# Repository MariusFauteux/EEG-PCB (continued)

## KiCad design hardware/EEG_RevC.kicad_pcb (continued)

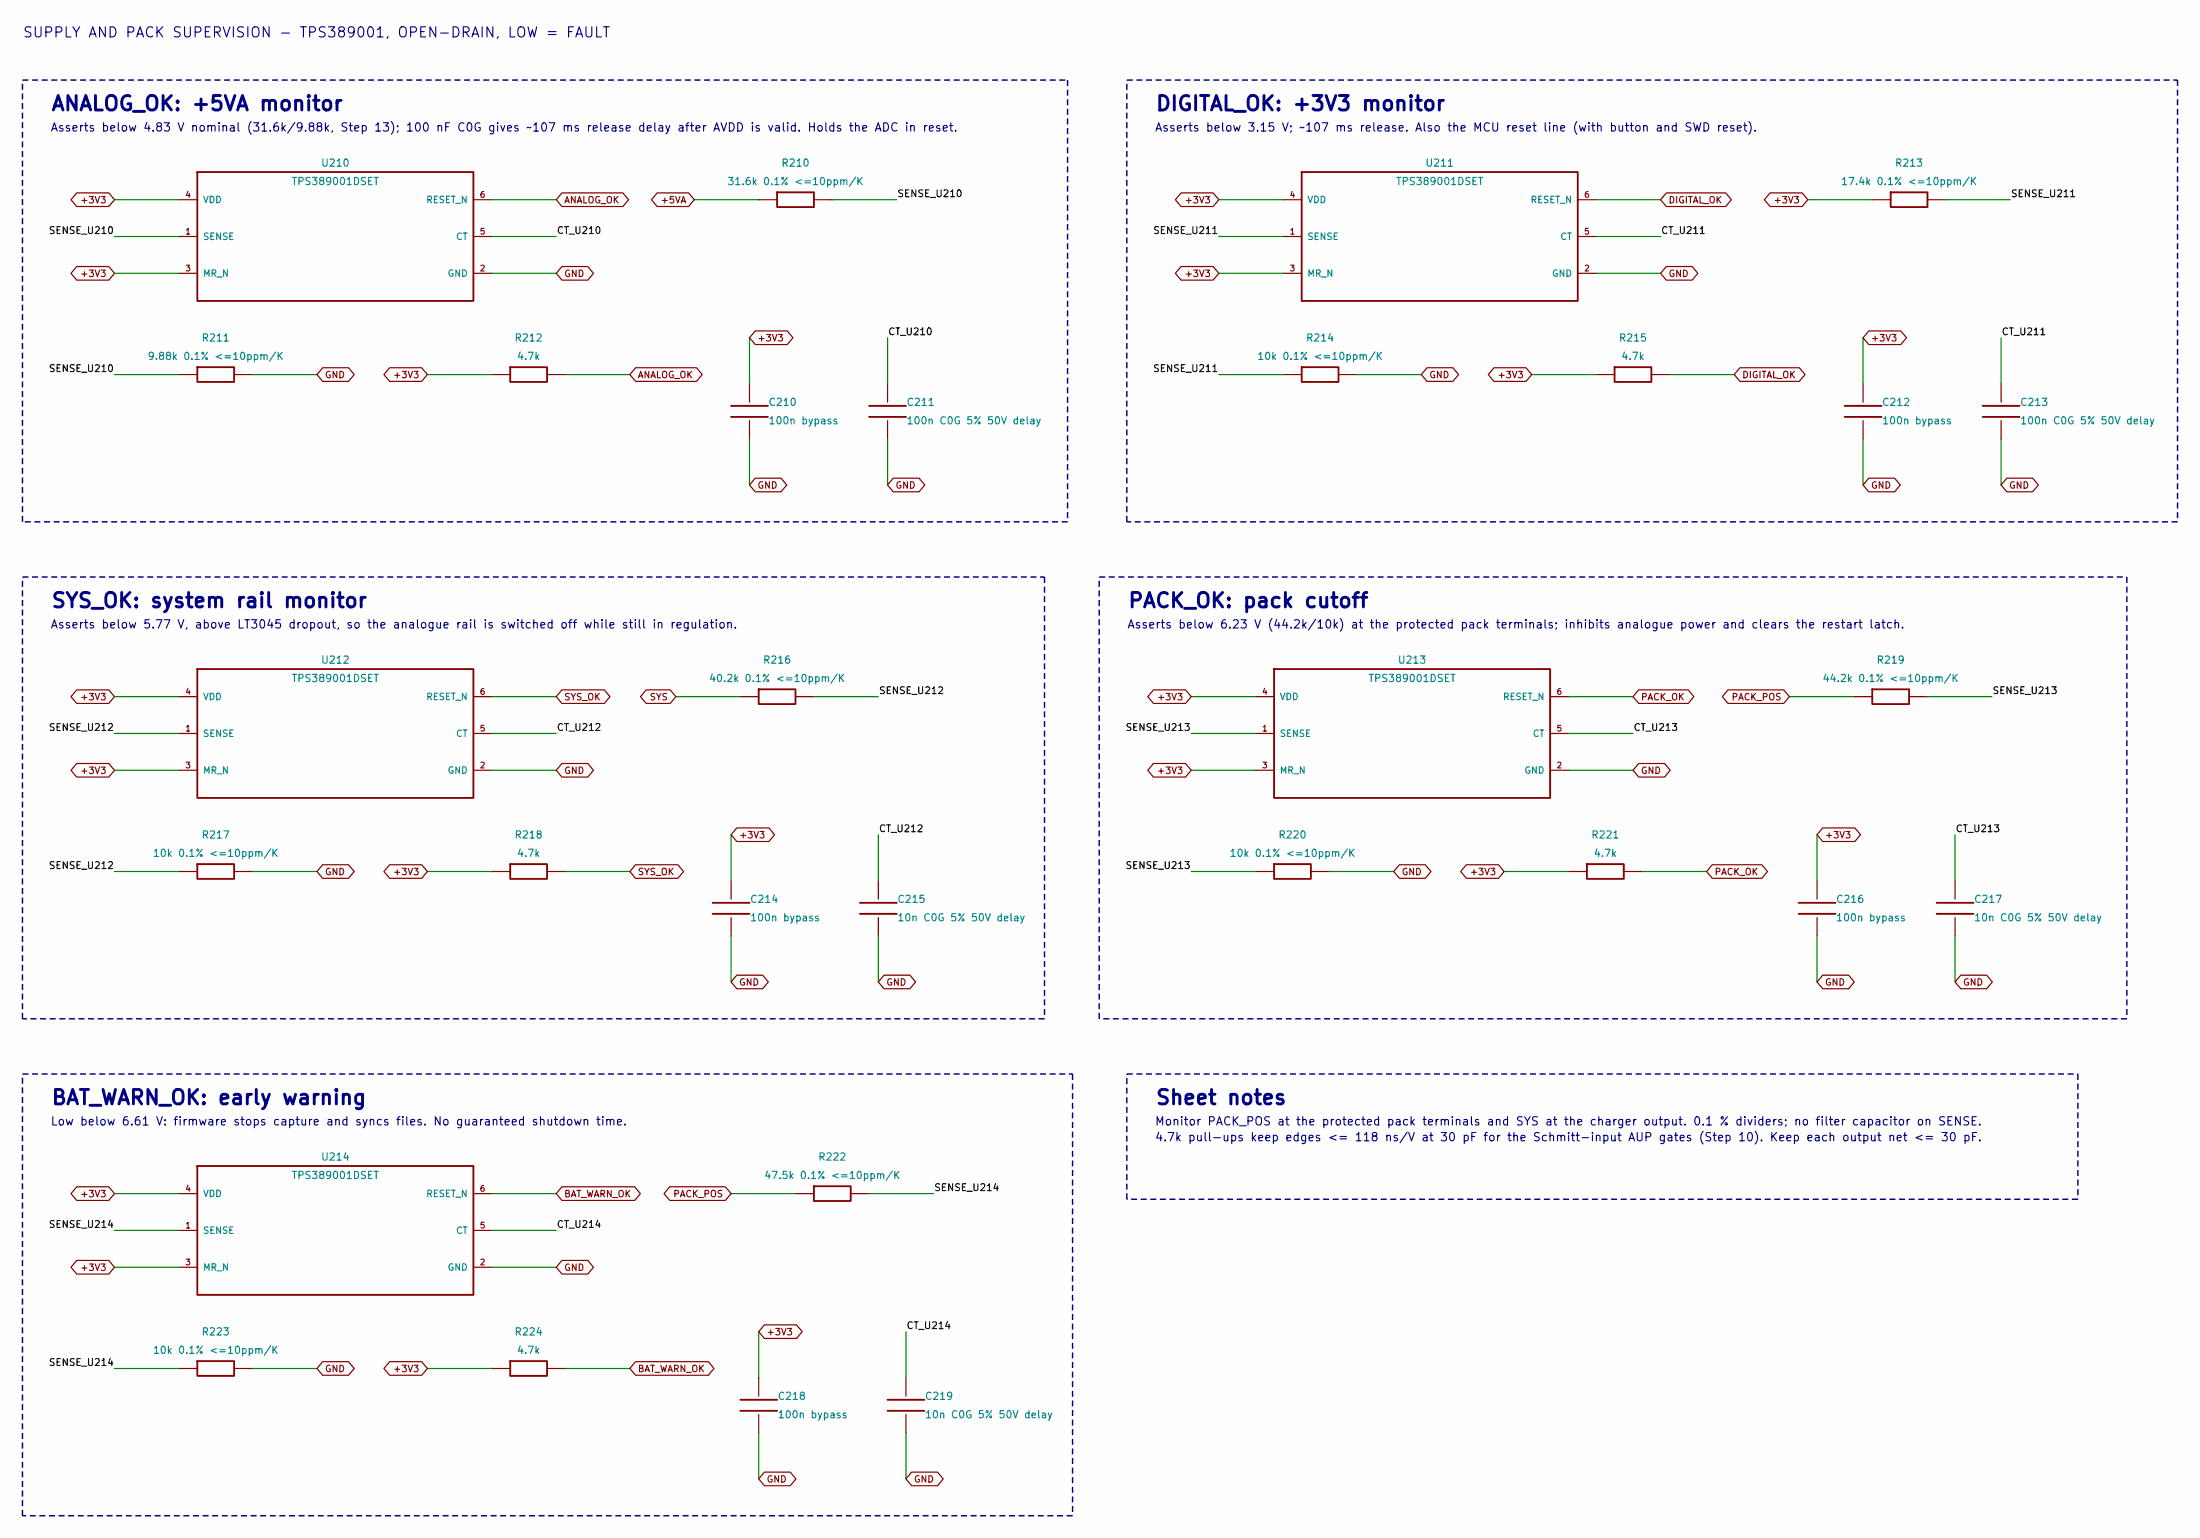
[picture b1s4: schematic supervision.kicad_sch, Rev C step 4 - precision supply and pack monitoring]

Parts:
C210, C212, C214, C216, C218: 100n bypass; C_0603_1608Metric; MPN GCM188R71H104KA57D
C211, C213: 100n C0G 5% 50V delay; C_1206_3216Metric; MPN GRM31C5C1H104JA01L
C215, C217, C219: 10n C0G 5% 50V delay; C_0603_1608Metric; MPN GCM1885C1H103JA16D
R210: 31.6k 0.1% <=10ppm/K; R_0603_1608Metric; MPN ERA-3ARB3162V
R211: 9.88k 0.1% <=10ppm/K; R_0603_1608Metric; MPN ERA-3ARB9881V
R212, R215, R218, R221, R224: 4.7k; R_0603_1608Metric; MPN ERJ-3EKF4701V
R213: 17.4k 0.1% <=10ppm/K; R_0603_1608Metric; MPN ERA-3ARB1742V
R214, R217, R220, R223: 10k 0.1% <=10ppm/K; R_0603_1608Metric; MPN ERA-3ARB103V
R216: 40.2k 0.1% <=10ppm/K; R_0603_1608Metric; MPN ERA-3ARB4022V
R219: 44.2k 0.1% <=10ppm/K; R_0603_1608Metric; MPN ERA-3ARB4422V
R222: 47.5k 0.1% <=10ppm/K; R_0603_1608Metric; MPN ERA-3ARB4752V
U210, U211, U212, U213, U214: TPS389001DSET; WSON-6_1.5x1.5mm_P0.5mm; MPN TPS389001DSET

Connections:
+3V3: C210.1, C212.1, C214.1, C216.1, C218.1, R212.1, R213.1, R215.1, R218.1, R221.1, R224.1, U210.3 (MR_N), U210.4 (VDD), U211.3 (MR_N), U211.4 (VDD), U212.3 (MR_N), U212.4 (VDD), U213.3 (MR_N), U213.4 (VDD), U214.3 (MR_N), U214.4 (VDD); also elsewhere on the board
+5VA: R210.1; also elsewhere on the board
/supervision/CT_U210: C211.1, U210.5 (CT)
/supervision/CT_U211: C213.1, U211.5 (CT)
/supervision/CT_U212: C215.1, U212.5 (CT)
/supervision/CT_U213: C217.1, U213.5 (CT)
/supervision/CT_U214: C219.1, U214.5 (CT)
/supervision/SENSE_U210: R210.2, R211.1, U210.1 (SENSE)
/supervision/SENSE_U211: R213.2, R214.1, U211.1 (SENSE)
/supervision/SENSE_U212: R216.2, R217.1, U212.1 (SENSE)
/supervision/SENSE_U213: R219.2, R220.1, U213.1 (SENSE)
/supervision/SENSE_U214: R222.2, R223.1, U214.1 (SENSE)
ANALOG_OK: R212.2, U210.6 (RESET_N); also elsewhere on the board
BAT_WARN_OK: R224.2, U214.6 (RESET_N); also elsewhere on the board
DIGITAL_OK: R215.2, U211.6 (RESET_N); also elsewhere on the board
GND: C210.2, C211.2, C212.2, C213.2, C214.2, C215.2, C216.2, C217.2, C218.2, C219.2, R211.2, R214.2, R217.2, R220.2, R223.2, U210.2 (GND), U211.2 (GND), U212.2 (GND), U213.2 (GND), U214.2 (GND); also elsewhere on the board
PACK_OK: R221.2, U213.6 (RESET_N); also elsewhere on the board
PACK_POS: R219.1, R222.1; also elsewhere on the board
SYS: R216.1; also elsewhere on the board
SYS_OK: R218.2, U212.6 (RESET_N); also elsewhere on the board

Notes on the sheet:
SUPPLY AND PACK SUPERVISION - TPS389001, OPEN-DRAIN, LOW = FAULT
ANALOG_OK: +5VA monitor
Asserts below 4.83 V nominal (31.6k/9.88k, Step 13); 100 nF C0G gives ~107 ms release delay after AVDD is valid. Holds the ADC in reset.
DIGITAL_OK: +3V3 monitor
Asserts below 3.15 V; ~107 ms release. Also the MCU reset line (with button and SWD reset).
SYS_OK: system rail monitor
Asserts below 5.77 V, above LT3045 dropout, so the analogue rail is switched off while still in regulation.
PACK_OK: pack cutoff
Asserts below 6.23 V (44.2k/10k) at the protected pack terminals; inhibits analogue power and clears the restart latch.
BAT_WARN_OK: early warning
Low below 6.61 V: firmware stops capture and syncs files. No guaranteed shutdown time.
Sheet notes
Monitor PACK_POS at the protected pack terminals and SYS at the charger output. 0.1 % dividers; no filter capacitor on SENSE.
4.7k pull-ups keep edges <= 118 ns/V at 30 pF for the Schmitt-input AUP gates (Step 10). Keep each output net <= 30 pF.

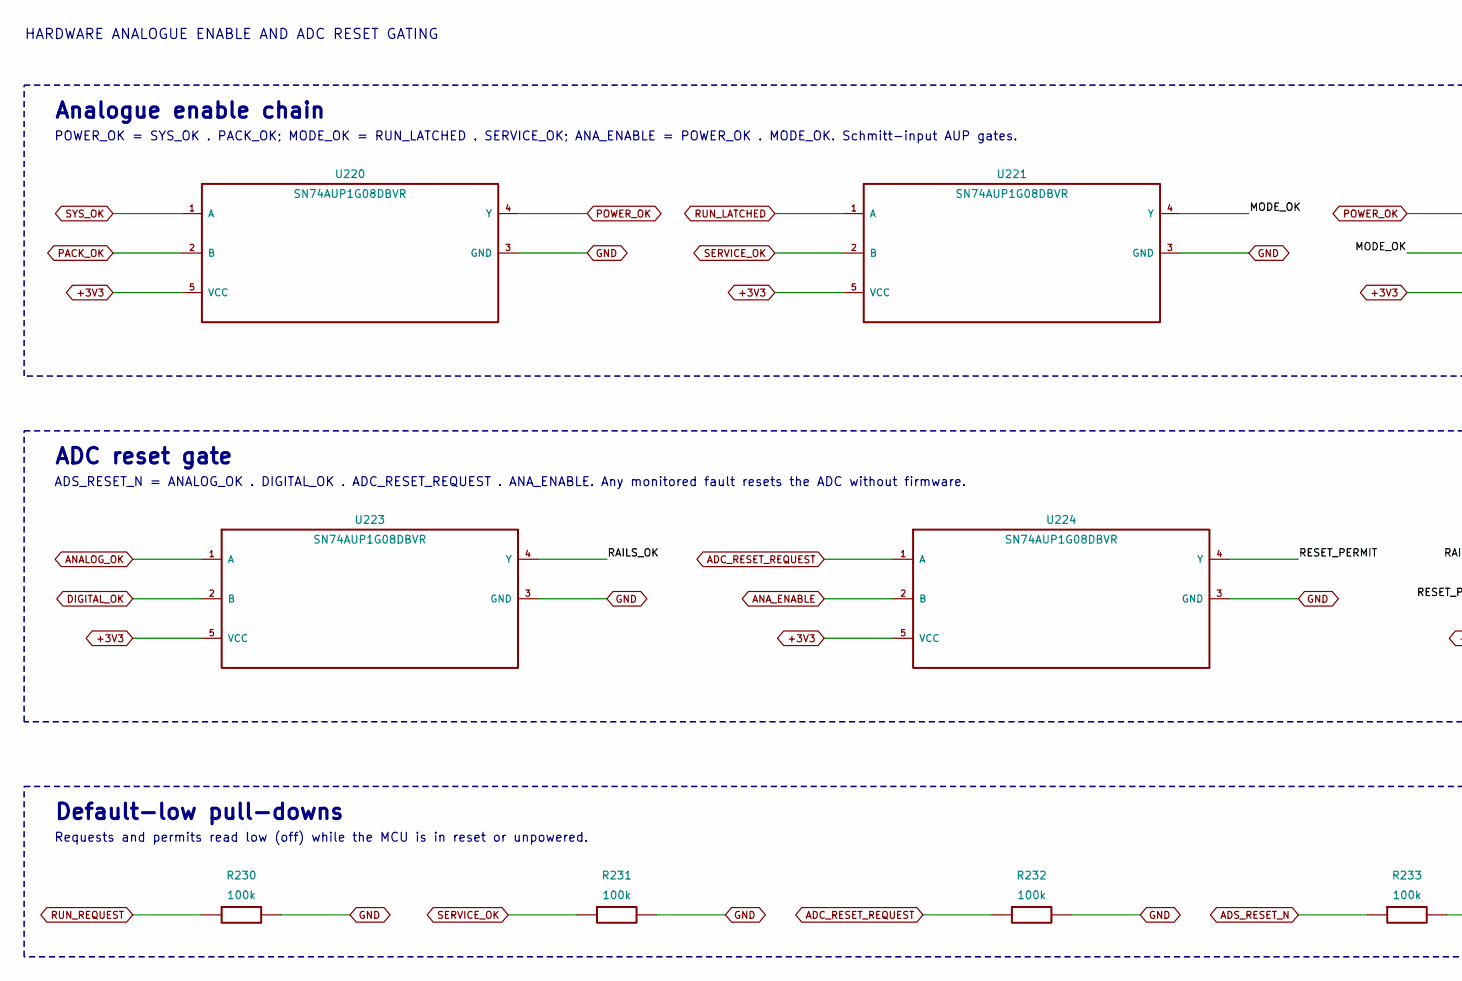
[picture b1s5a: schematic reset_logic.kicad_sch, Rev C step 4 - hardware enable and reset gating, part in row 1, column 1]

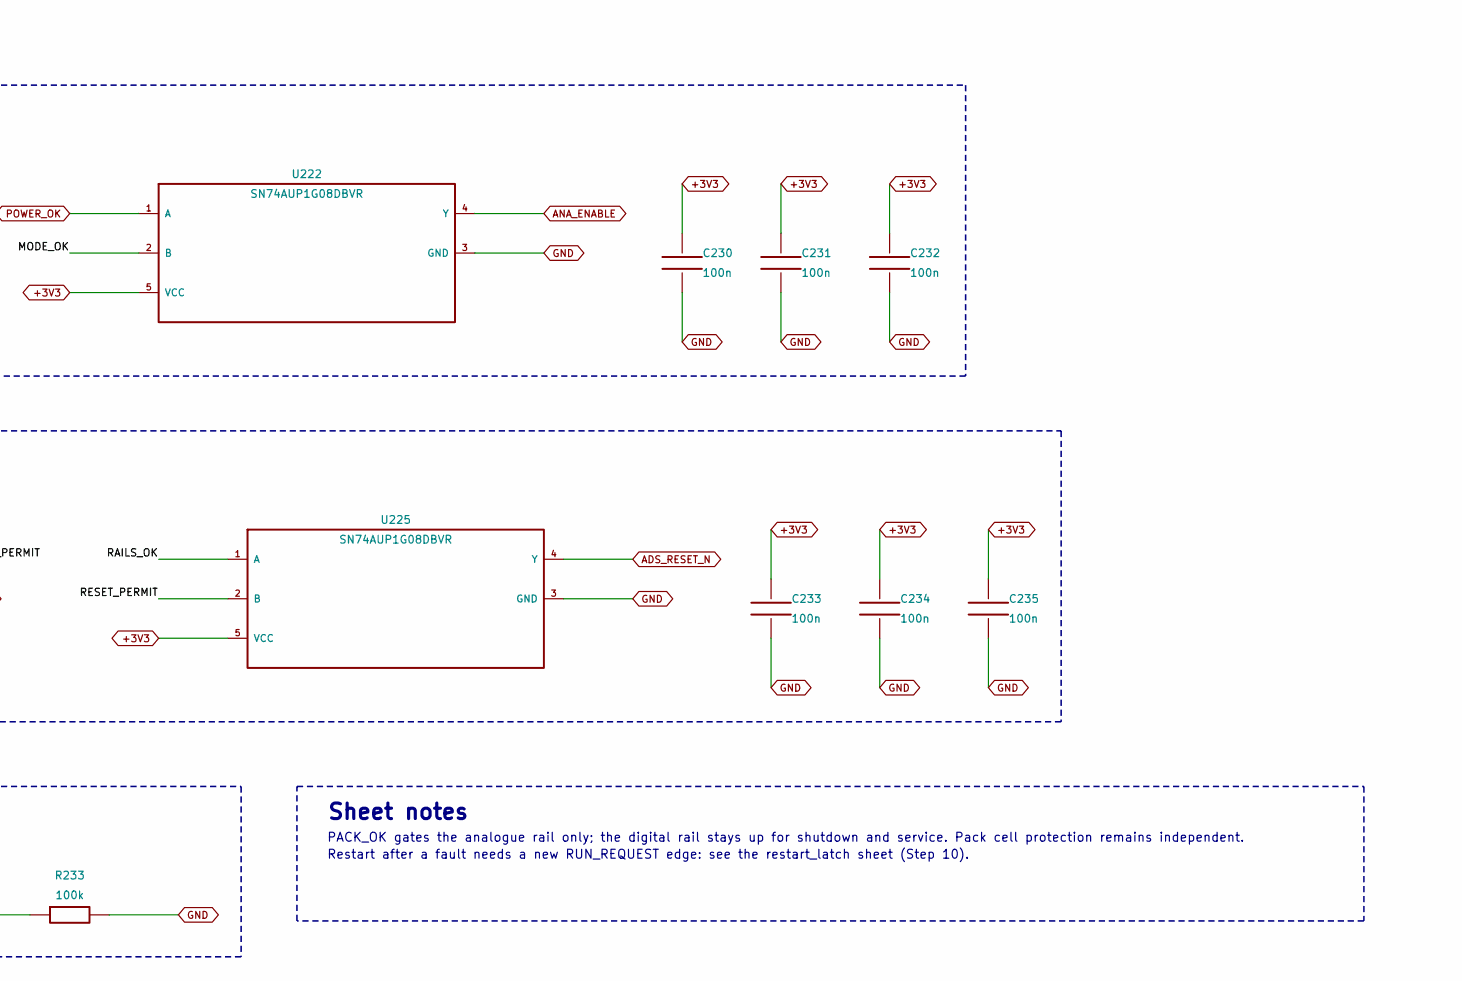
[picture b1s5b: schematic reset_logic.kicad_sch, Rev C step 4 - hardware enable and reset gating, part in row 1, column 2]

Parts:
C230, C231, C232, C233, C234, C235: 100n; C_0603_1608Metric; MPN GCM188R71H104KA57D
R230, R231, R232, R233: 100k; R_0603_1608Metric; MPN ERJ-3EKF1003V
U220, U221, U222, U223, U224, U225: SN74AUP1G08DBVR; SOT-23-5; MPN SN74AUP1G08DBVR

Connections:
+3V3: C230.1, C231.1, C232.1, C233.1, C234.1, C235.1, U220.5 (VCC), U221.5 (VCC), U222.5 (VCC), U223.5 (VCC), U224.5 (VCC), U225.5 (VCC); also elsewhere on the board
/reset logic/MODE_OK: U221.4 (Y), U222.2 (B)
/reset logic/RAILS_OK: U223.4 (Y), U225.1 (A)
/reset logic/RESET_PERMIT: U224.4 (Y), U225.2 (B)
ADC_RESET_REQUEST: R232.1, U224.1 (A); also elsewhere on the board
ADS_RESET_N: R233.1, U225.4 (Y); also elsewhere on the board
ANALOG_OK: U223.1 (A); also elsewhere on the board
ANA_ENABLE: U222.4 (Y), U224.2 (B); also elsewhere on the board
DIGITAL_OK: U223.2 (B); also elsewhere on the board
GND: C230.2, C231.2, C232.2, C233.2, C234.2, C235.2, R230.2, R231.2, R232.2, R233.2, U220.3 (GND), U221.3 (GND), U222.3 (GND), U223.3 (GND), U224.3 (GND), U225.3 (GND); also elsewhere on the board
PACK_OK: U220.2 (B); also elsewhere on the board
POWER_OK: U220.4 (Y), U222.1 (A); also elsewhere on the board
RUN_LATCHED: U221.1 (A); also elsewhere on the board
RUN_REQUEST: R230.1; also elsewhere on the board
SERVICE_OK: R231.1, U221.2 (B); also elsewhere on the board
SYS_OK: U220.1 (A); also elsewhere on the board

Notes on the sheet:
HARDWARE ANALOGUE ENABLE AND ADC RESET GATING
Analogue enable chain
POWER_OK = SYS_OK . PACK_OK; MODE_OK = RUN_LATCHED . SERVICE_OK; ANA_ENABLE = POWER_OK . MODE_OK. Schmitt-input AUP gates.
ADC reset gate
ADS_RESET_N = ANALOG_OK . DIGITAL_OK . ADC_RESET_REQUEST . ANA_ENABLE. Any monitored fault resets the ADC without firmware.
Default-low pull-downs
Requests and permits read low (off) while the MCU is in reset or unpowered.
Sheet notes
PACK_OK gates the analogue rail only; the digital rail stays up for shutdown and service. Pack cell protection remains independent.
Restart after a fault needs a new RUN_REQUEST edge: see the restart_latch sheet (Step 10).

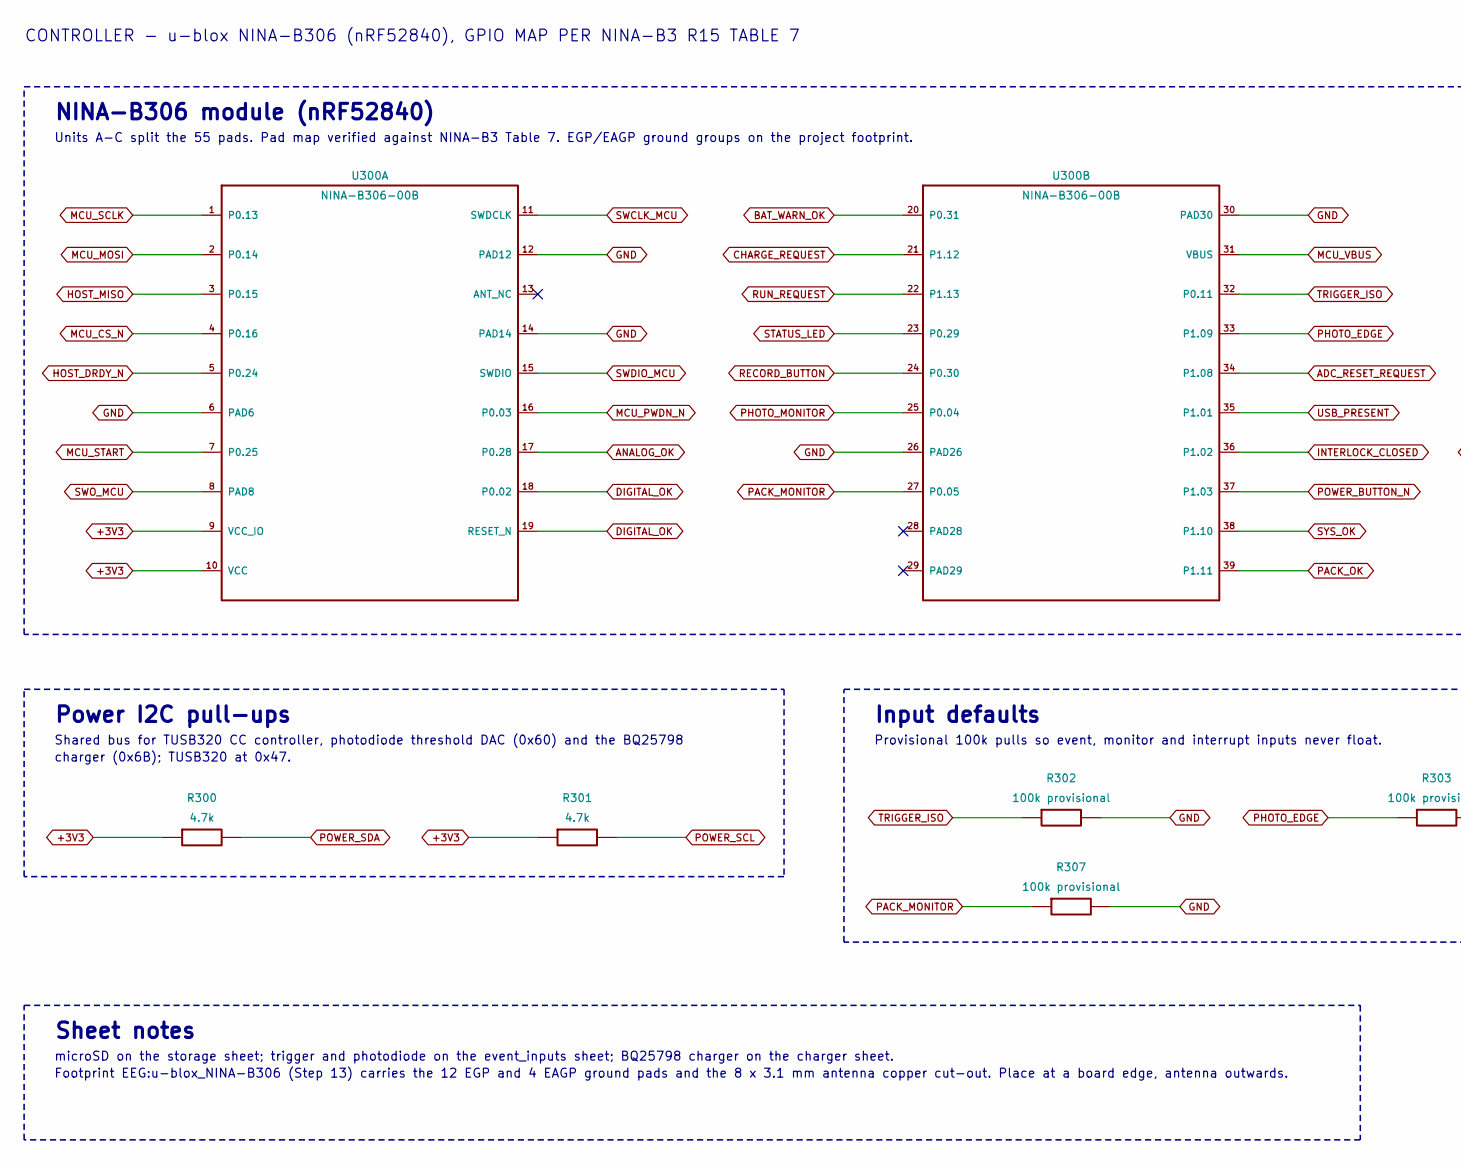
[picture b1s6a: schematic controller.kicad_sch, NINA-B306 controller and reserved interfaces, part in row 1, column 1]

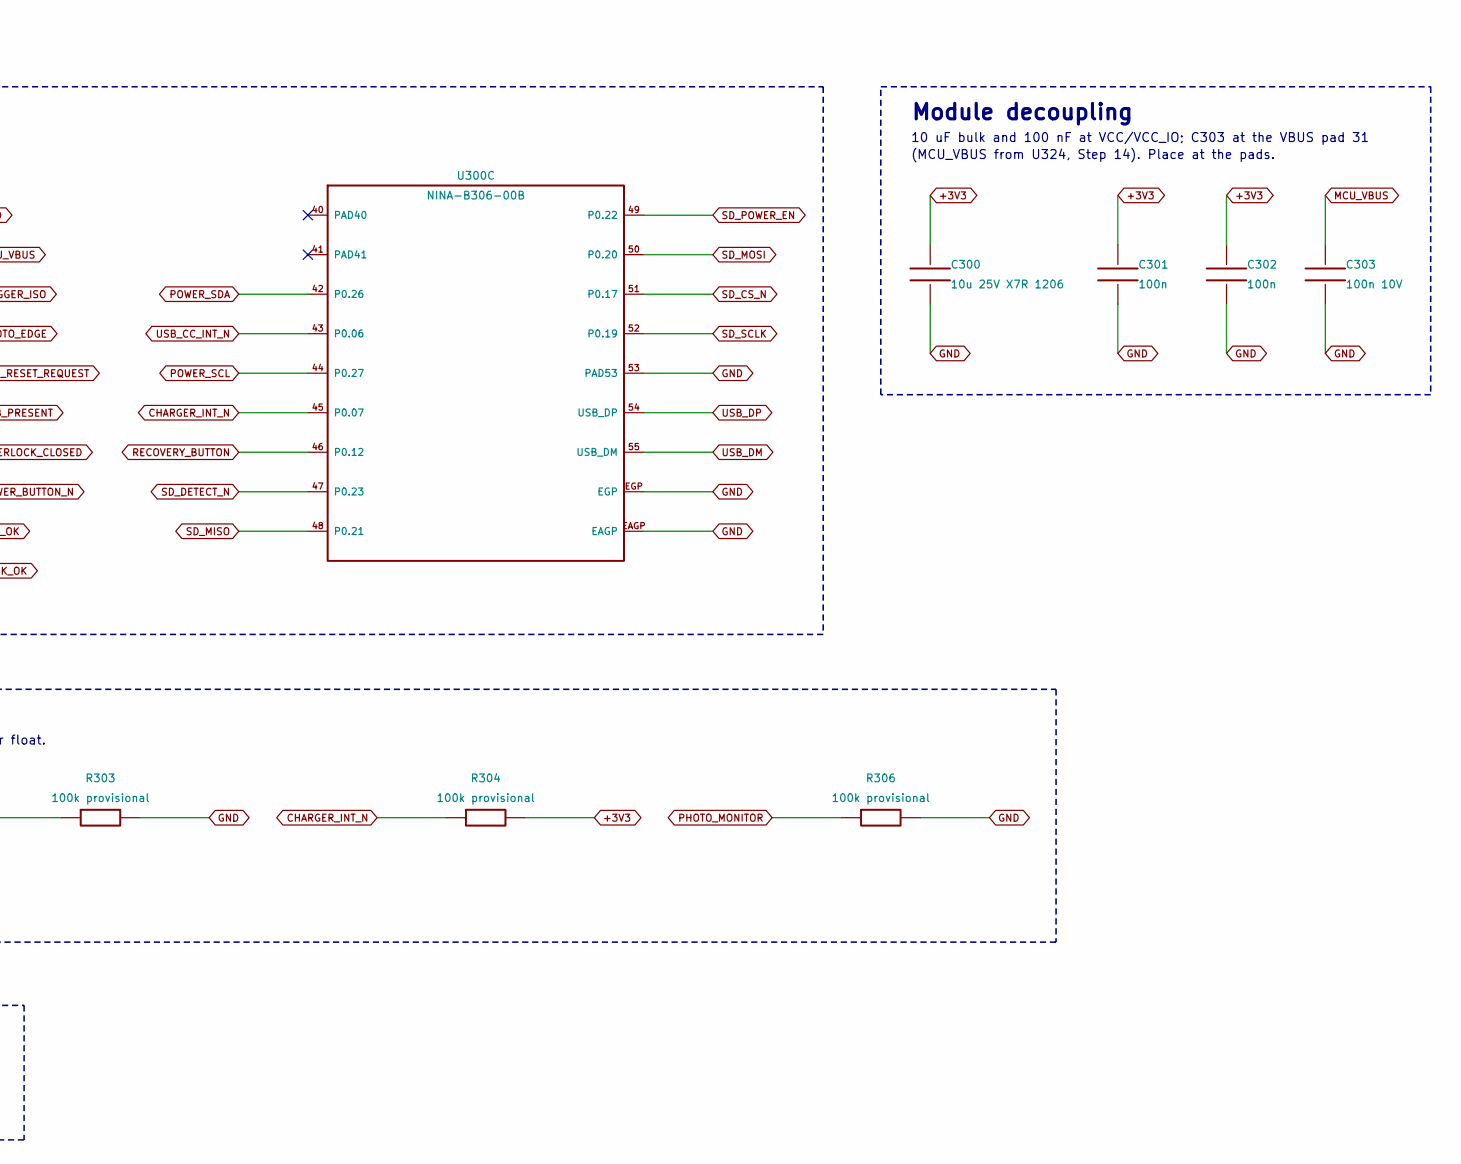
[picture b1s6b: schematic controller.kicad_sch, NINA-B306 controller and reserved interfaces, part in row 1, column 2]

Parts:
C300: 10u 25V X7R 1206; C_1206_3216Metric; MPN GRM31CR71E106KA12L
C301, C302: 100n; C_0603_1608Metric; MPN GCM188R71H104KA57D
C303: 100n 10V; C_0603_1608Metric; MPN GCM188R71H104KA57D
R300, R301: 4.7k; R_0603_1608Metric; MPN ERJ-3EKF4701V
R302, R303, R304, R306, R307: 100k provisional; R_0603_1608Metric; MPN ERJ-3EKF1003V
U300: NINA-B306-00B; u-blox_NINA-B306; MPN NINA-B306-00B

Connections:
+3V3: C300.1, C301.1, C302.1, R300.1, R301.1, R304.2, U300.9 (VCC_IO), U300.10 (VCC); also elsewhere on the board
ADC_RESET_REQUEST: U300.34 (P1.08); also elsewhere on the board
ANALOG_OK: U300.17 (P0.28); also elsewhere on the board
BAT_WARN_OK: U300.20 (P0.31); also elsewhere on the board
CHARGER_INT_N: R304.1, U300.45 (P0.07); also elsewhere on the board
CHARGE_REQUEST: U300.21 (P1.12); also elsewhere on the board
DIGITAL_OK: U300.18 (P0.02), U300.19 (RESET_N); also elsewhere on the board
GND: C300.2, C301.2, C302.2, C303.2, R302.2, R303.2, R306.2, R307.2, U300.6, U300.12, U300.14, U300.26, U300.30, U300.53, U300.EAGP, U300.EGP; also elsewhere on the board
HOST_DRDY_N: U300.5 (P0.24); also elsewhere on the board
HOST_MISO: U300.3 (P0.15); also elsewhere on the board
INTERLOCK_CLOSED: U300.36 (P1.02); also elsewhere on the board
MCU_CS_N: U300.4 (P0.16); also elsewhere on the board
MCU_MOSI: U300.2 (P0.14); also elsewhere on the board
MCU_PWDN_N: U300.16 (P0.03); also elsewhere on the board
MCU_SCLK: U300.1 (P0.13); also elsewhere on the board
MCU_START: U300.7 (P0.25); also elsewhere on the board
MCU_VBUS: C303.1, U300.31 (VBUS); also elsewhere on the board
PACK_MONITOR: R307.1, U300.27 (P0.05)
PACK_OK: U300.39 (P1.11); also elsewhere on the board
PHOTO_EDGE: R303.1, U300.33 (P1.09); also elsewhere on the board
PHOTO_MONITOR: R306.1, U300.25 (P0.04); also elsewhere on the board
POWER_BUTTON_N: U300.37 (P1.03); also elsewhere on the board
POWER_SCL: R301.2, U300.44 (P0.27); also elsewhere on the board
POWER_SDA: R300.2, U300.42 (P0.26); also elsewhere on the board
RECORD_BUTTON: U300.24 (P0.30); also elsewhere on the board
RECOVERY_BUTTON: U300.46 (P0.12); also elsewhere on the board
RUN_REQUEST: U300.22 (P1.13); also elsewhere on the board
SD_CS_N: U300.51 (P0.17); also elsewhere on the board
SD_DETECT_N: U300.47 (P0.23); also elsewhere on the board
SD_MISO: U300.48 (P0.21); also elsewhere on the board
SD_MOSI: U300.50 (P0.20); also elsewhere on the board
SD_POWER_EN: U300.49 (P0.22); also elsewhere on the board
SD_SCLK: U300.52 (P0.19); also elsewhere on the board
STATUS_LED: U300.23 (P0.29); also elsewhere on the board
SWCLK_MCU: U300.11 (SWDCLK); also elsewhere on the board
SWDIO_MCU: U300.15 (SWDIO); also elsewhere on the board
SWO_MCU: U300.8; also elsewhere on the board
SYS_OK: U300.38 (P1.10); also elsewhere on the board
TRIGGER_ISO: R302.1, U300.32 (P0.11); also elsewhere on the board
USB_CC_INT_N: U300.43 (P0.06); also elsewhere on the board
USB_DM: U300.55 (USB_DM); also elsewhere on the board
USB_DP: U300.54 (USB_DP); also elsewhere on the board
USB_PRESENT: U300.35 (P1.01); also elsewhere on the board

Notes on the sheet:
CONTROLLER - u-blox NINA-B306 (nRF52840), GPIO MAP PER NINA-B3 R15 TABLE 7
NINA-B306 module (nRF52840)
Units A-C split the 55 pads. Pad map verified against NINA-B3 Table 7. EGP/EAGP ground groups on the project footprint.
Module decoupling
10 uF bulk and 100 nF at VCC/VCC_IO; C303 at the VBUS pad 31
(MCU_VBUS from U324, Step 14). Place at the pads.
Power I2C pull-ups
Shared bus for TUSB320 CC controller, photodiode threshold DAC (0x60) and the BQ25798
charger (0x6B); TUSB320 at 0x47.
Input defaults
Provisional 100k pulls so event, monitor and interrupt inputs never float.
Sheet notes
microSD on the storage sheet; trigger and photodiode on the event_inputs sheet; BQ25798 charger on the charger sheet.
Footprint EEG:u-blox_NINA-B306 (Step 13) carries the 12 EGP and 4 EAGP ground pads and the 8 x 3.1 mm antenna copper cut-out. Place at a board edge, antenna outwards.

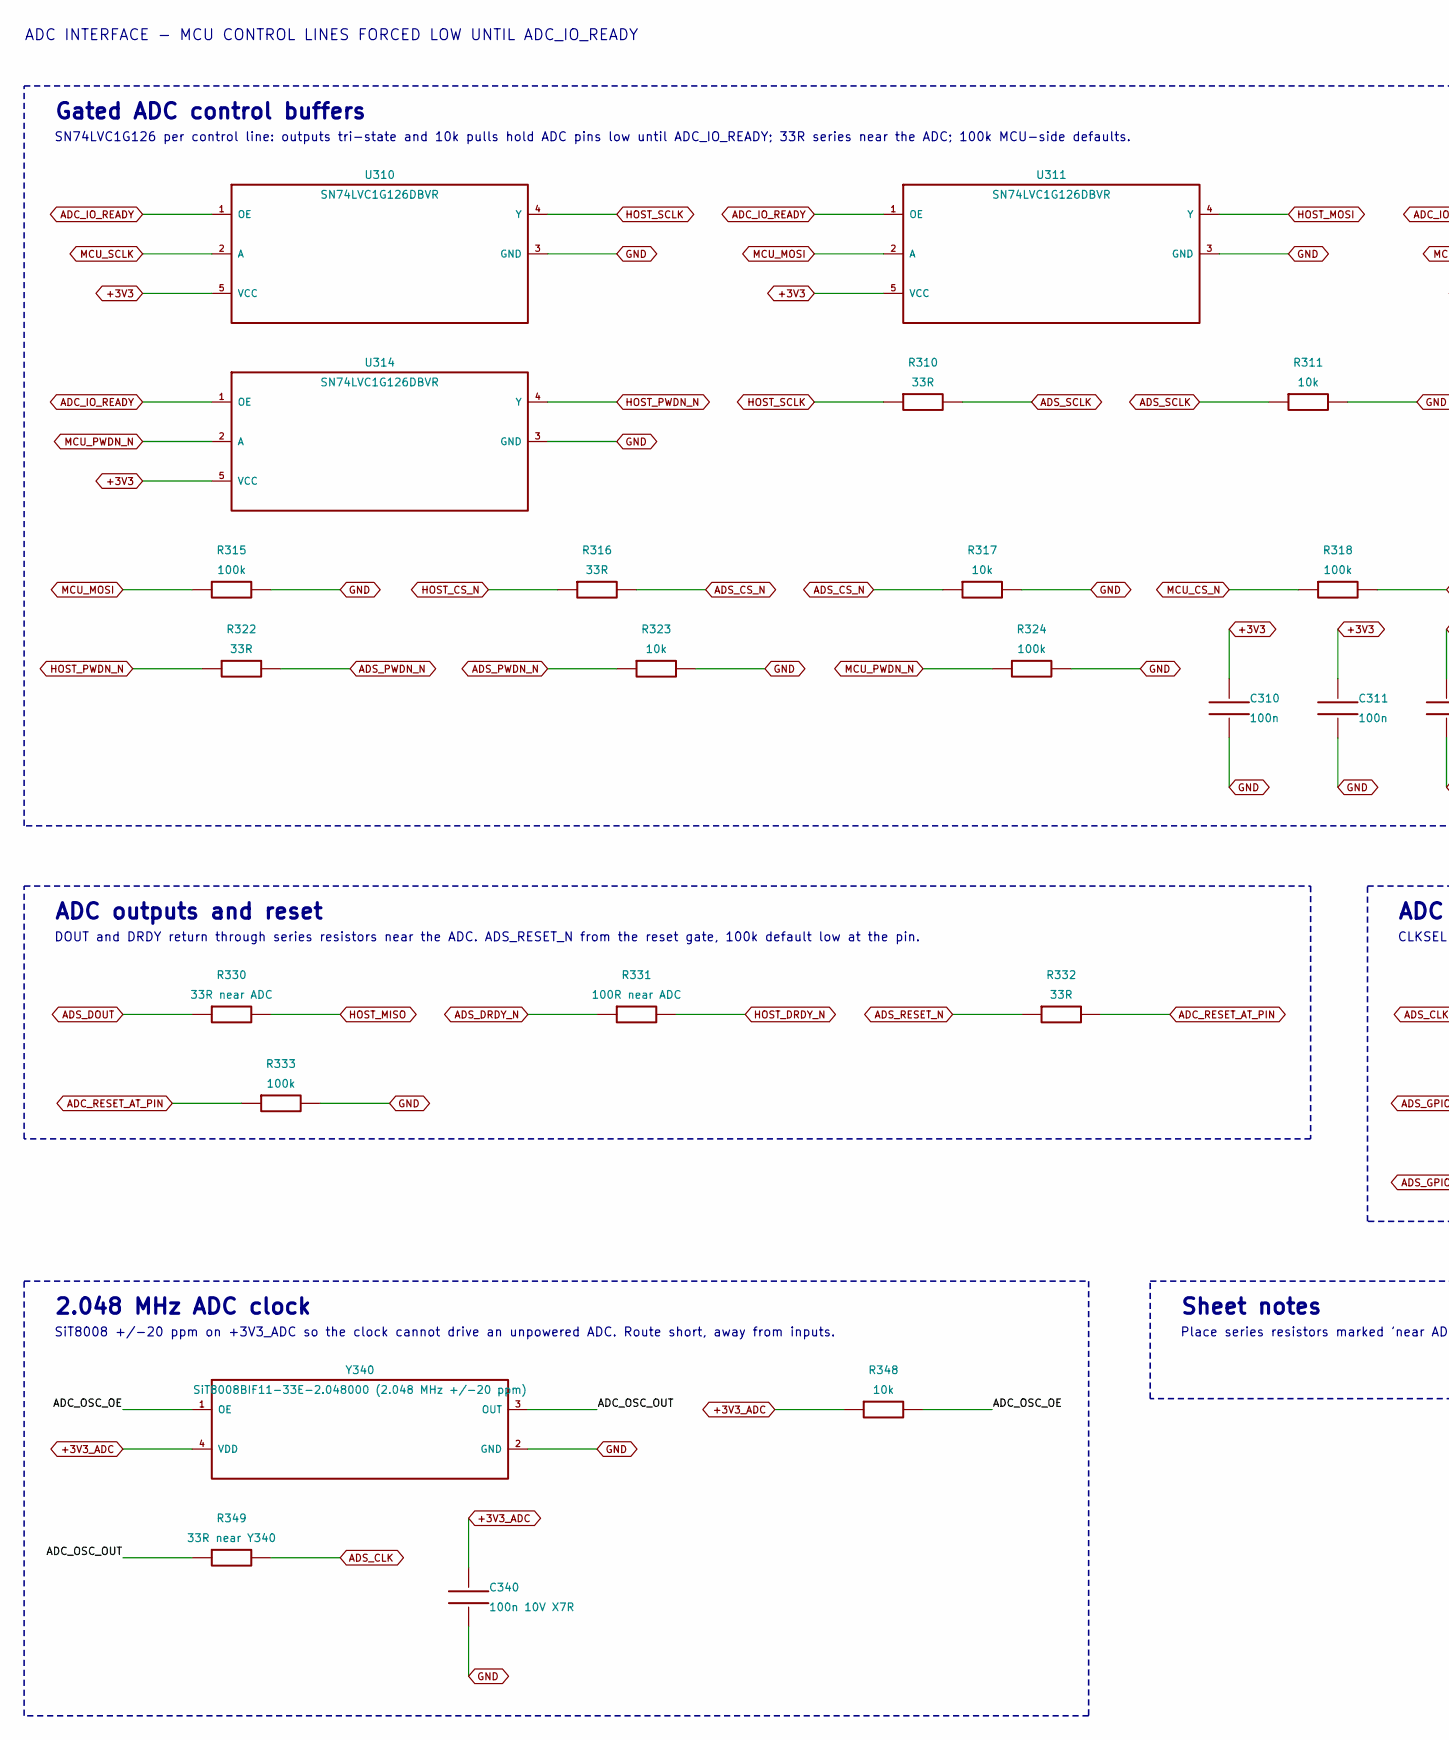
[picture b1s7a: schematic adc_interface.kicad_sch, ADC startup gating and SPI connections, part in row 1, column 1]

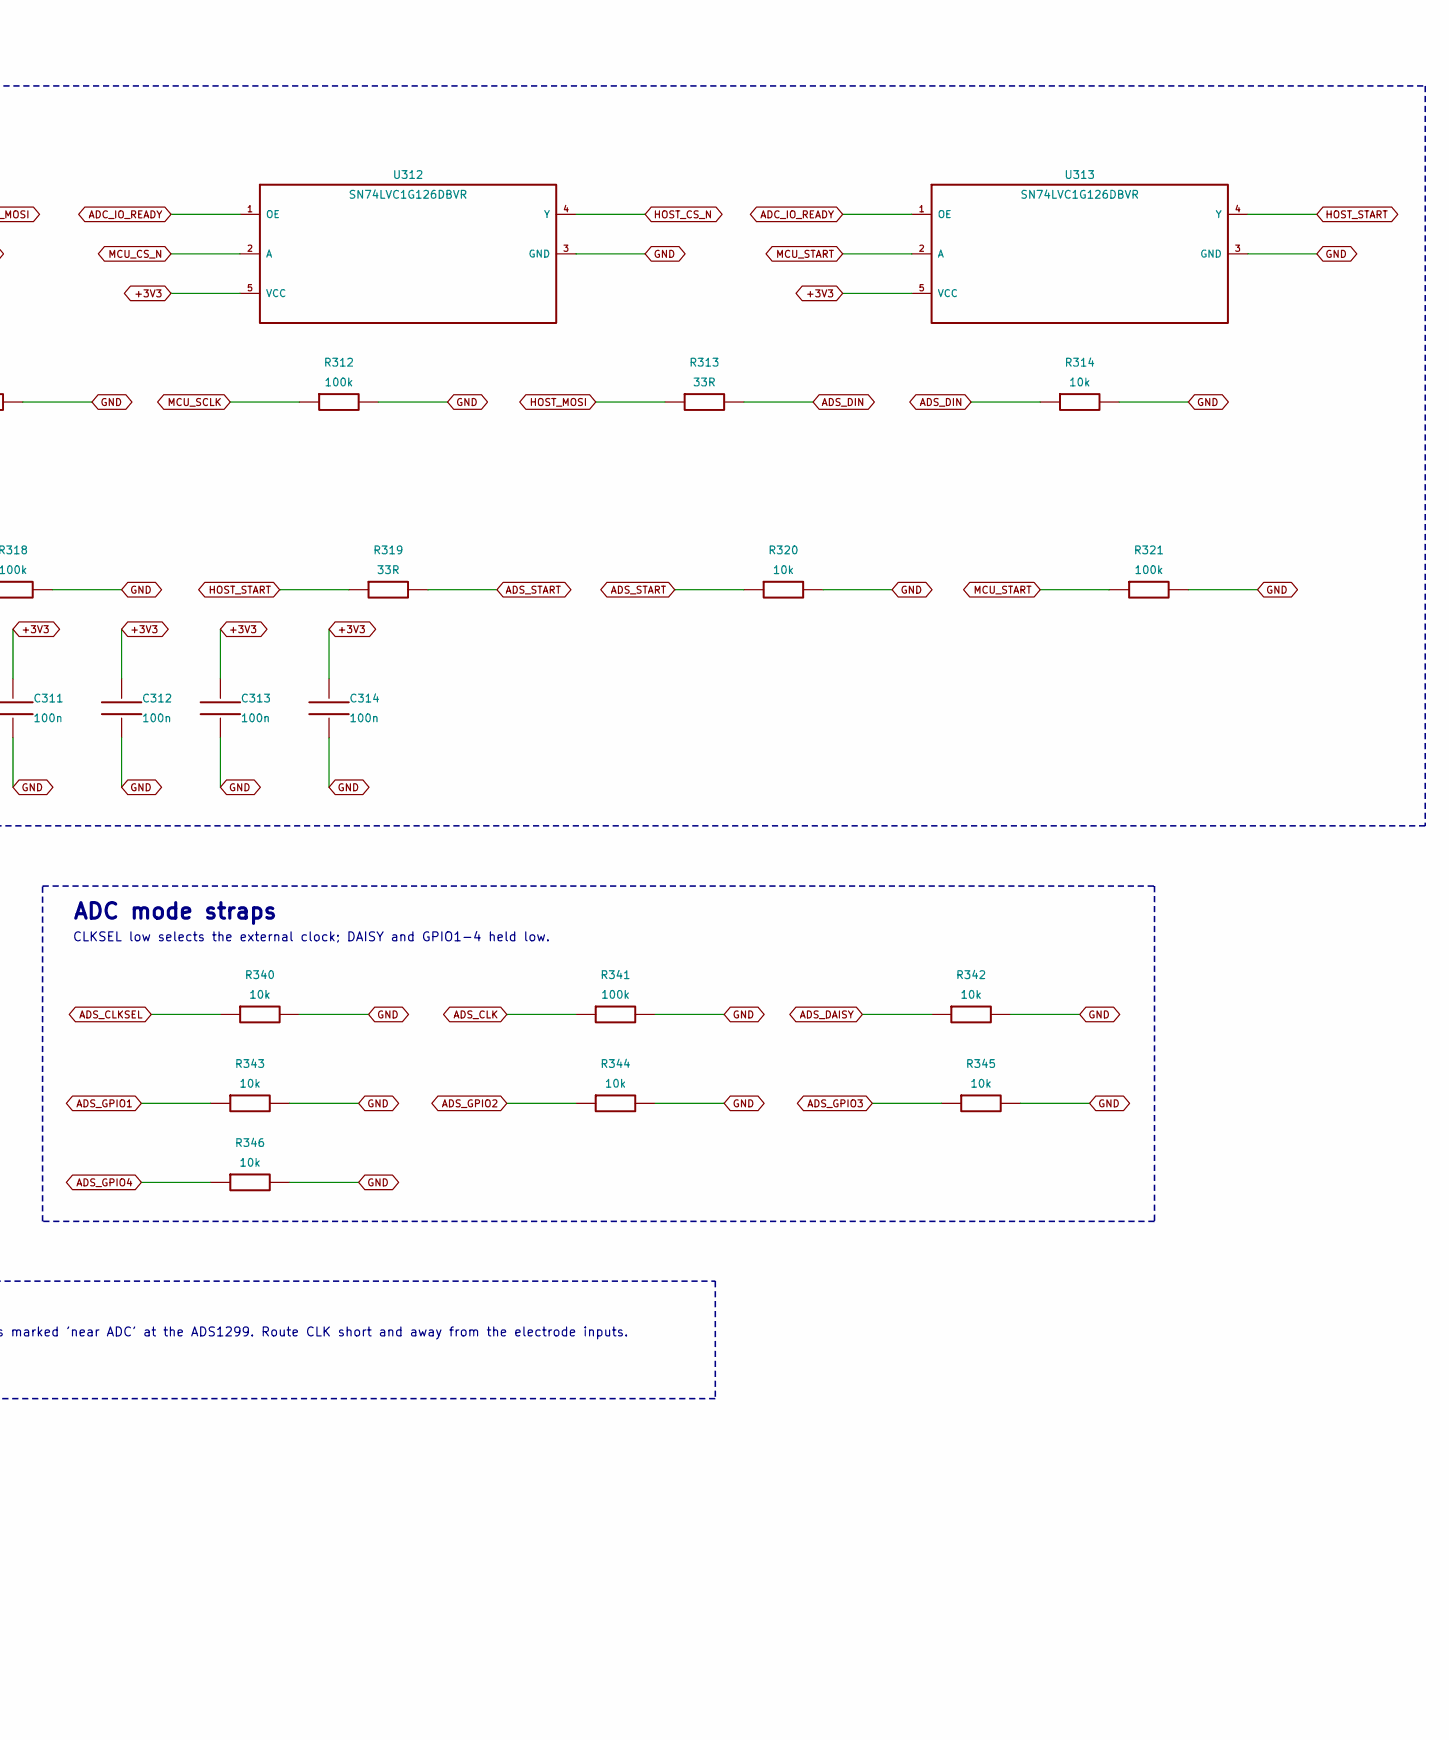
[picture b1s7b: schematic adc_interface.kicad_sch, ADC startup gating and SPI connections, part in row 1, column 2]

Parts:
C310, C311, C312, C313, C314: 100n; C_0603_1608Metric; MPN GCM188R71H104KA57D
C340: 100n 10V X7R; C_0603_1608Metric; MPN GCM188R71H104KA57D
R310, R313, R316, R319, R322, R332: 33R; R_0603_1608Metric; MPN ERJ-3EKF33R0V
R311, R314, R317, R320, R323, R340, R342, R343, R344, R345, R346, R348: 10k; R_0603_1608Metric; MPN ERJ-3EKF1002V
R312, R315, R318, R321, R324, R333, R341: 100k; R_0603_1608Metric; MPN ERJ-3EKF1003V
R330: 33R near ADC; R_0603_1608Metric; MPN ERJ-3EKF33R0V
R331: 100R near ADC; R_0603_1608Metric; MPN ERJ-3EKF1000V
R349: 33R near Y340; R_0603_1608Metric; MPN ERJ-3EKF33R0V
U310, U311, U312, U313, U314: SN74LVC1G126DBVR; SOT-23-5; MPN SN74LVC1G126DBVR
Y340: SiT8008BIF11-33E-2.048000 (2.048 MHz +/-20 ppm); Oscillator_SMD_SiT_PQFN-4Pin_2.5x2.0mm; MPN SIT8008BIF11-33E-2.048000

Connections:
+3V3: C310.1, C311.1, C312.1, C313.1, C314.1, U310.5 (VCC), U311.5 (VCC), U312.5 (VCC), U313.5 (VCC), U314.5 (VCC); also elsewhere on the board
+3V3_ADC: C340.1, R348.1, Y340.4 (VDD); also elsewhere on the board
/ADC startup gating and SPI connections/ADC_OSC_OE: R348.2, Y340.1 (OE)
/ADC startup gating and SPI connections/ADC_OSC_OUT: R349.1, Y340.3 (OUT)
ADC_IO_READY: U310.1 (OE), U311.1 (OE), U312.1 (OE), U313.1 (OE), U314.1 (OE); also elsewhere on the board
ADC_RESET_AT_PIN: R332.2, R333.1; also elsewhere on the board
ADS_CLK: R341.1, R349.2; also elsewhere on the board
ADS_CLKSEL: R340.1; also elsewhere on the board
ADS_CS_N: R316.2, R317.1; also elsewhere on the board
ADS_DAISY: R342.1; also elsewhere on the board
ADS_DIN: R313.2, R314.1; also elsewhere on the board
ADS_DOUT: R330.1; also elsewhere on the board
ADS_DRDY_N: R331.1; also elsewhere on the board
ADS_GPIO1: R343.1; also elsewhere on the board
ADS_GPIO2: R344.1; also elsewhere on the board
ADS_GPIO3: R345.1; also elsewhere on the board
ADS_GPIO4: R346.1; also elsewhere on the board
ADS_PWDN_N: R322.2, R323.1; also elsewhere on the board
ADS_RESET_N: R332.1; also elsewhere on the board
ADS_SCLK: R310.2, R311.1; also elsewhere on the board
ADS_START: R319.2, R320.1; also elsewhere on the board
GND: C310.2, C311.2, C312.2, C313.2, C314.2, C340.2, R311.2, R312.2, R314.2, R315.2, R317.2, R318.2, R320.2, R321.2, R323.2, R324.2, R333.2, R340.2, R341.2, R342.2, R343.2, R344.2, R345.2, R346.2, U310.3 (GND), U311.3 (GND), U312.3 (GND), U313.3 (GND), U314.3 (GND), Y340.2 (GND); also elsewhere on the board
HOST_CS_N: R316.1, U312.4 (Y)
HOST_DRDY_N: R331.2; also elsewhere on the board
HOST_MISO: R330.2; also elsewhere on the board
HOST_MOSI: R313.1, U311.4 (Y)
HOST_PWDN_N: R322.1, U314.4 (Y)
HOST_SCLK: R310.1, U310.4 (Y)
HOST_START: R319.1, U313.4 (Y)
MCU_CS_N: R318.1, U312.2 (A); also elsewhere on the board
MCU_MOSI: R315.1, U311.2 (A); also elsewhere on the board
MCU_PWDN_N: R324.1, U314.2 (A); also elsewhere on the board
MCU_SCLK: R312.1, U310.2 (A); also elsewhere on the board
MCU_START: R321.1, U313.2 (A); also elsewhere on the board

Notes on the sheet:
ADC INTERFACE - MCU CONTROL LINES FORCED LOW UNTIL ADC_IO_READY
Gated ADC control buffers
SN74LVC1G126 per control line: outputs tri-state and 10k pulls hold ADC pins low until ADC_IO_READY; 33R series near the ADC; 100k MCU-side defaults.
ADC outputs and reset
DOUT and DRDY return through series resistors near the ADC. ADS_RESET_N from the reset gate, 100k default low at the pin.
ADC mode straps
CLKSEL low selects the external clock; DAISY and GPIO1-4 held low.
2.048 MHz ADC clock
SiT8008 +/-20 ppm on +3V3_ADC so the clock cannot drive an unpowered ADC. Route short, away from inputs.
Sheet notes
Place series resistors marked 'near ADC' at the ADS1299. Route CLK short and away from the electrode inputs.
